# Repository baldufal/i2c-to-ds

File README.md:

# DS to I2C Expander
Software for Atmega**8 for connecting up to 40 DS18b20 devices to one I2C bus.

We have many DS sensors and didn't want to/couldn't connect them all to a Raspberry Pi due to lack of pins.
We therefore created a small breakout board with an ATmega168(L) on it to read the sensors and make readings available via I2C.
The devices are connected to 4 1-wire buses, which can be searched and read out through setting bits in the control register at `0x00`.

## Board
The board provides 4 independent 1-Wire buses with 4 3-pin connectors each.
The DS are powered by 5V, but the data line is pulled up to 3.3V (which is the supply voltage of the Atmega).

Additionally there are 7 GPIO pins on the board, that can also be controlled via I2C.

For monitoring/debugging, there are 2 LEDs that indicate working 3.3V and 5V voltages.
Another 2 LEDs are controlled by the mC and indicate healthy operation (blinking @ 1Hz) and ongoing readouts (second LED on).

## I2C Interface
The device address is `0x3f`.
The I2C interface exposes 254 8bit registers:
Register | Semantics | Allowed values (writing)
---|---|---
0 | Controlling 1-Wire buses | 1 / 2 / 4 / 8 / 16
1 | GPIO Data Direction | 0-127
2 | GPIO Values | 0-127
3 | CRC over following bytes| -
4 | Length n | -
5 | Data Byte 1 | -
6 | Data Byte 2| -
7 | ... | -
n+4 | Data Byte n-1 | -

- Register 1 allows reading/setting the data direction (input or output) of the 7 GPIO pins.
- Register 2 allows reading the state of input GPIOs and setting the state of output GPIOs.
- The CRC is the 1-Wire CRC8. It is computed over register 4 and the following (actually used!) data bytes (end defined by the content of register 4).
- Register 4 contains the number of data bytes that follow. All other registers will read as 0.

During 1-Wire operations, no I2C communication is possible (interrupts disabled)!

## 1-Wire commands
The four 1-Wire buses can be controlled by setting any of the 5 LSBs in the command register (only one at a time).

Bits 0 to 3 will trigger a device search on the corresponding 1-Wire bus.
After ~1s, the data bytes will contain an ordered list of all addresses on this bus.

Bit 4 will trigger the conversion (actual measurement of temperatures by DSs) of all devices on all buses.
After ~1s, the data bytes will contain the temperature data. This consists of 2 bytes per DS, as specified in the data sheet.

The conversion command depends on the 1-Wire addresses, that were previously found by the device search command(s).
A search on bus 0 will first reset all addresses. A search on any bus must not be triggered after a search on a bus with higher index was triggered.
It is thereby strongly advised to set bits 0 to 3 in this order for initialization and then only set bit 3 for readout.

## Test scripts
There are two python scripts, that allow sending 1-Wire commands and reading/setting GPIO values from a terminal on a Raspberry Pi.

## License
MIT, but would be nice if you would link back here.

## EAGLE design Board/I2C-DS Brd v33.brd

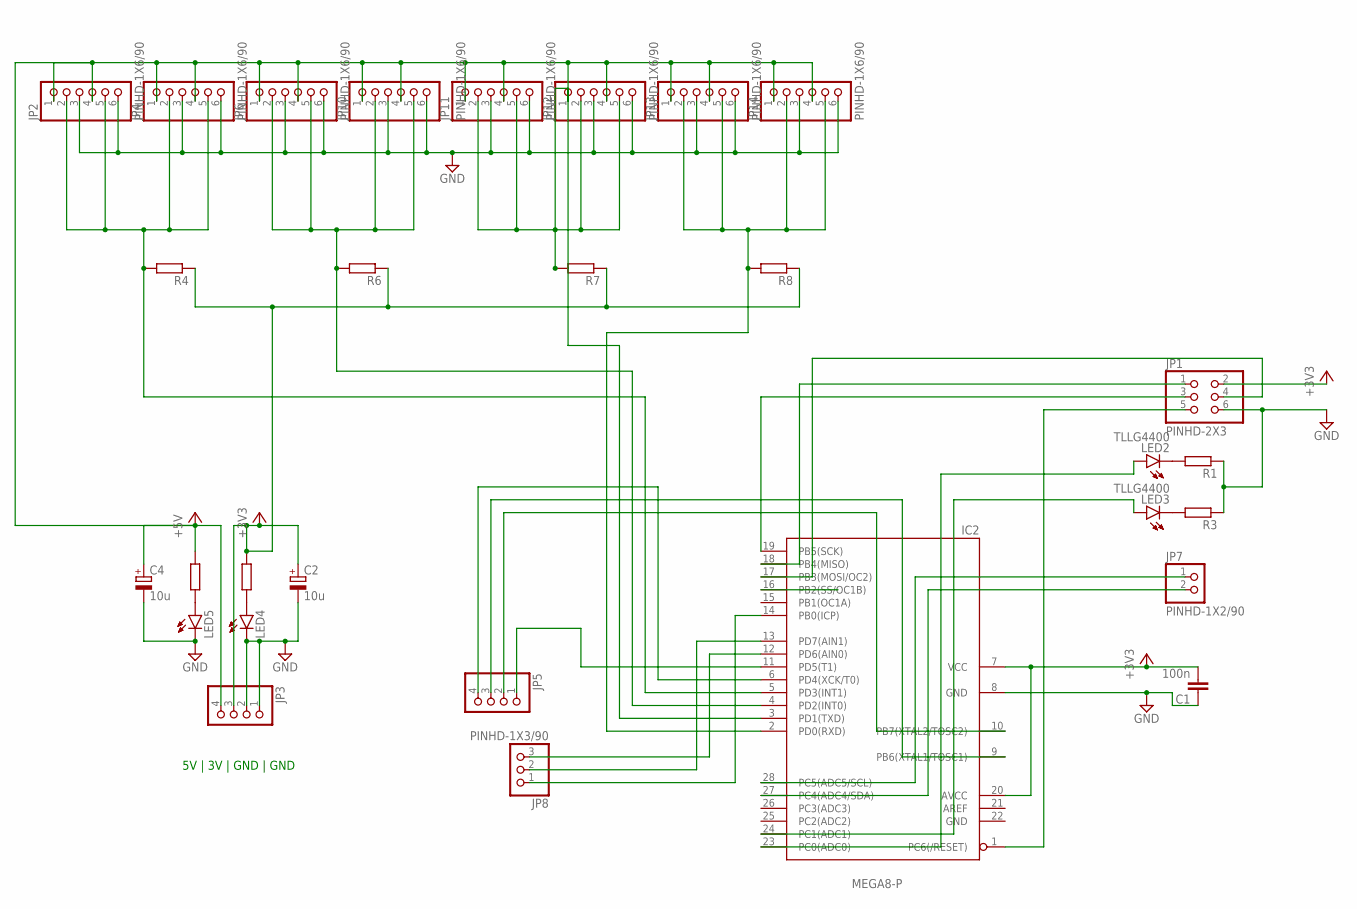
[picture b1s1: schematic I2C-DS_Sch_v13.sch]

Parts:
C1: 100n; C050-030X075
C2, C4: 10u; E2,5-7
IC2: MEGA8-P; DIL28-3
JP1: PINHD-2X3; 2X03
JP2, JP4, JP6, JP10, JP11, JP12, JP13, JP14: PINHD-1X6/90; 1X06/90
JP3, JP5: PINHD-1X4/90; 1X04/90
JP7: PINHD-1X2/90; 1X02/90
JP8: PINHD-1X3/90; 1X03/90
LED2, LED3: TLLG4400; LED3MM
LED4, LED5: LED3MM
R1, R3, R4, R6, R7, R8, R9, R10: R-EU_0207/10; 0207/10

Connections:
+3V3: C1.2, C2.+, IC2.7 (VCC), IC2.20 (AVCC), JP1.2, JP3.3, R4.1, R6.1, R7.1, R8.1, R9.1
+5V: C4.+, JP2.1, JP2.4, JP3.4, JP4.1, JP4.4, JP6.1, JP6.4, JP10.1, JP10.4, JP11.1, JP11.4, JP12.1, JP12.4, JP13.1, JP13.4, JP14.1, JP14.4, R10.1
GND: C1.1, C2.-, C4.-, IC2.8 (GND), IC2.22 (GND), JP1.6, JP2.3, JP2.6, JP3.1, JP3.2, JP4.3, JP4.6, JP6.3, JP6.6, JP10.3, JP10.6, JP11.3, JP11.6, JP12.3, JP12.6, JP13.3, JP13.6, JP14.3, JP14.6, LED4.K (C), LED5.K (C), R1.1, R3.1
unnamed: IC2.23 (PC0(ADC0)), LED2.A
unnamed: LED2.K (C), R1.2
unnamed: LED3.K (C), R3.2
unnamed: IC2.3 (PD1(TXD)), JP11.2, JP11.5, JP12.2, JP12.5, R7.2
unnamed: IC2.2 (PD0(RXD)), JP13.2, JP13.5, JP14.2, JP14.5, R8.2
unnamed: LED5.A, R10.2
unnamed: IC2.13 (PD7(AIN1)), JP8.2
unnamed: IC2.1 (PC6(/RESET)), JP1.5
unnamed: IC2.19 (PB5(SCK)), JP1.3
unnamed: IC2.18 (PB4(MISO)), JP1.1
unnamed: IC2.17 (PB3(MOSI/OC2)), JP1.4
unnamed: IC2.6 (PD4(XCK/T0)), JP5.4
unnamed: IC2.11 (PD5(T1)), JP5.1
unnamed: IC2.9 (PB6(XTAL1/TOSC1)), JP5.3
unnamed: IC2.10 (PB7(XTAL2/TOSC2)), JP5.2
unnamed: IC2.27 (PC4(ADC4/SDA)), JP7.2
unnamed: IC2.28 (PC5(ADC5/SCL)), JP7.1
unnamed: IC2.24 (PC1(ADC1)), LED3.A
unnamed: IC2.12 (PD6(AIN0)), JP8.3
unnamed: IC2.14 (PB0(ICP)), JP8.1
unnamed: LED4.A, R9.2
unnamed: IC2.5 (PD3(INT1)), JP2.2, JP2.5, JP4.2, JP4.5, R4.2
unnamed: IC2.4 (PD2(INT0)), JP6.2, JP6.5, JP10.2, JP10.5, R6.2

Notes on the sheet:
5V | 3V | GND | GND

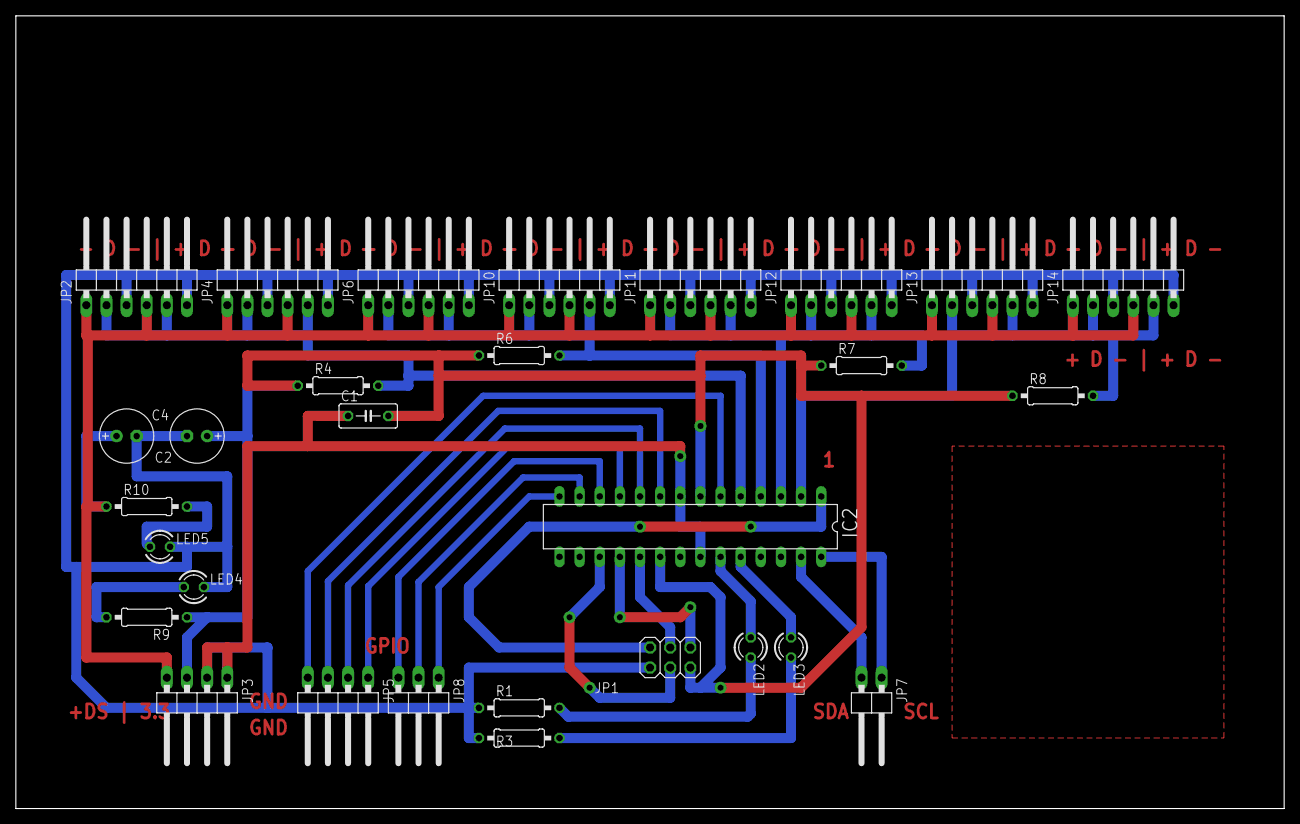
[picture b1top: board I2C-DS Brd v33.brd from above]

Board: 2 copper layers, 160.0 x 100.0 mm, 29 parts (0 on the bottom side), 26 nets.

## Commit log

2023-12-25 Add board and test files
2023-12-25 Mention device address
